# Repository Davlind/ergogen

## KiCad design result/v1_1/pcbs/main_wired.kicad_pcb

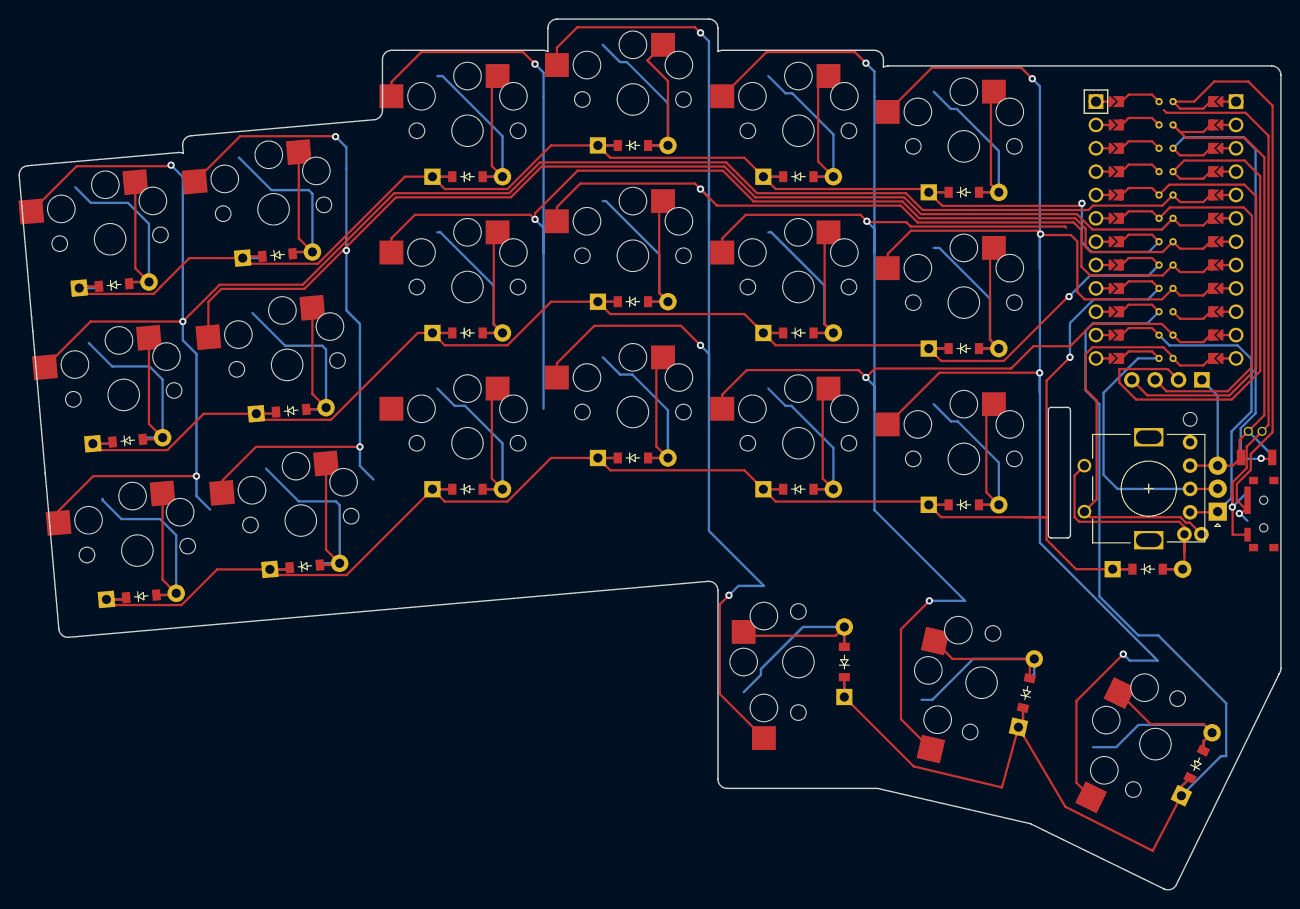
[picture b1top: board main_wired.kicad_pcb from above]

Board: 2 copper layers, 137.3 x 94.7 mm, 46 parts (0 on the bottom side), 39 nets.

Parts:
D1, D2, D3, D4, D5, D6, D7, D8, D9, D10, D11, D12, D13, D14, D15, D16, D17, D18, D19, D20, D21, D22: ComboDiode
MCU1: ProMicro
OLED1: OLED; OLED_headers
ROT1: rotary_encoder
S1, S2, S3, S4, S5, S6, S7, S8, S9, S10, S11, S12, S13, S14, S15, S16, S17, S18, S19, S20, S21: PG1350

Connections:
GND: MCU1.2, MCU1.21, MCU1.22, OLED1.1, ROT1.B
P2: MCU1.20, OLED1.4
P3: MCU1.19, OLED1.3
P4: D3.1, D3.2, D6.1, D6.2, D9.1, D9.2, D12.1, D12.2, D15.1, D15.2, D18.1, D18.2, MCU1.18
P5: D2.1, D2.2, D5.1, D5.2, D8.1, D8.2, D11.1, D11.2, D14.1, D14.2, D17.1, D17.2, MCU1.17
P6: D1.1, D1.2, D4.1, D4.2, D7.1, D7.2, D10.1, D10.2, D13.1, D13.2, D16.1, D16.2, D22.1, D22.2, MCU1.16
P7: D19.1, D19.2, D20.1, D20.2, D21.1, D21.2, MCU1.15
P8: MCU1.14, ROT1.A
P9: MCU1.13, ROT1.C
P10: MCU1.12, ROT1.1
P15: MCU1.9, S16.2, S17.2, S18.2, S21.2
P16: MCU1.11, S13.2, S14.2, S15.2, S20.2
P18: MCU1.8, S10.2, S11.2, S12.2, S19.2
P19: MCU1.7, S7.2, S8.2, S9.2
P20: MCU1.6, S4.2, S5.2, S6.2
P21: MCU1.5, S1.2, S2.2, S3.2
VCC: MCU1.4, OLED1.2
enc_diode: D22.1, D22.2, ROT1.2
home_thumb: D20.1, D20.2, S20.1
index_bottom: D13.1, D13.2, S13.1
index_home: D14.1, D14.2, S14.1
index_top: D15.1, D15.2, S15.1
inner_bottom: D16.1, D16.2, S16.1
inner_home: D17.1, D17.2, S17.1
inner_thumb: D21.1, D21.2, S21.1
inner_top: D18.1, D18.2, S18.1
middle_bottom: D10.1, D10.2, S10.1
middle_home: D11.1, D11.2, S11.1
middle_top: D12.1, D12.2, S12.1
outer_bottom: D1.1, D1.2, S1.1
outer_home: D2.1, D2.2, S2.1
outer_thumb: D19.1, D19.2, S19.1
outer_top: D3.1, D3.2, S3.1
pinky_bottom: D4.1, D4.2, S4.1
pinky_home: D5.1, D5.2, S5.1
pinky_top: D6.1, D6.2, S6.1
ring_bottom: D7.1, D7.2, S7.1
ring_home: D8.1, D8.2, S8.1
ring_top: D9.1, D9.2, S9.1

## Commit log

2022-07-09 misc
2023-06-26 No idea what this was
